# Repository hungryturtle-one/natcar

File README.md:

Natcar is a student design competition created in 1994 by Prof. Richard Spencer and engineers from National Semiconductor. UC Berkeley has been a long-time partner in the event. There is a final competition in May, generally held at UC Davis, in which many schools compete. Teams design, build and race autonomous vehicles on a track marked by 1″-wide white tape.

Originally, there was a wire carrying a 75 kHz sinusoidal signal (100 mA rms) under the tape and many teams sensed the magnetic field around the wire. Since 2016, we no longer provide the wire under the tape and the sensing must be done optically. The contest is intended for undergraduate students, but teams with graduate students, high-school students or student who have competed in a previous Natcar may attend the competition, although they will compete in a separate division.

from https://ece.ucdavis.edu/natcar

Was 6th place in the 2018 competition
https://www.youtube.com/watch?v=erOzUBIFhNc&feature=youtu.be

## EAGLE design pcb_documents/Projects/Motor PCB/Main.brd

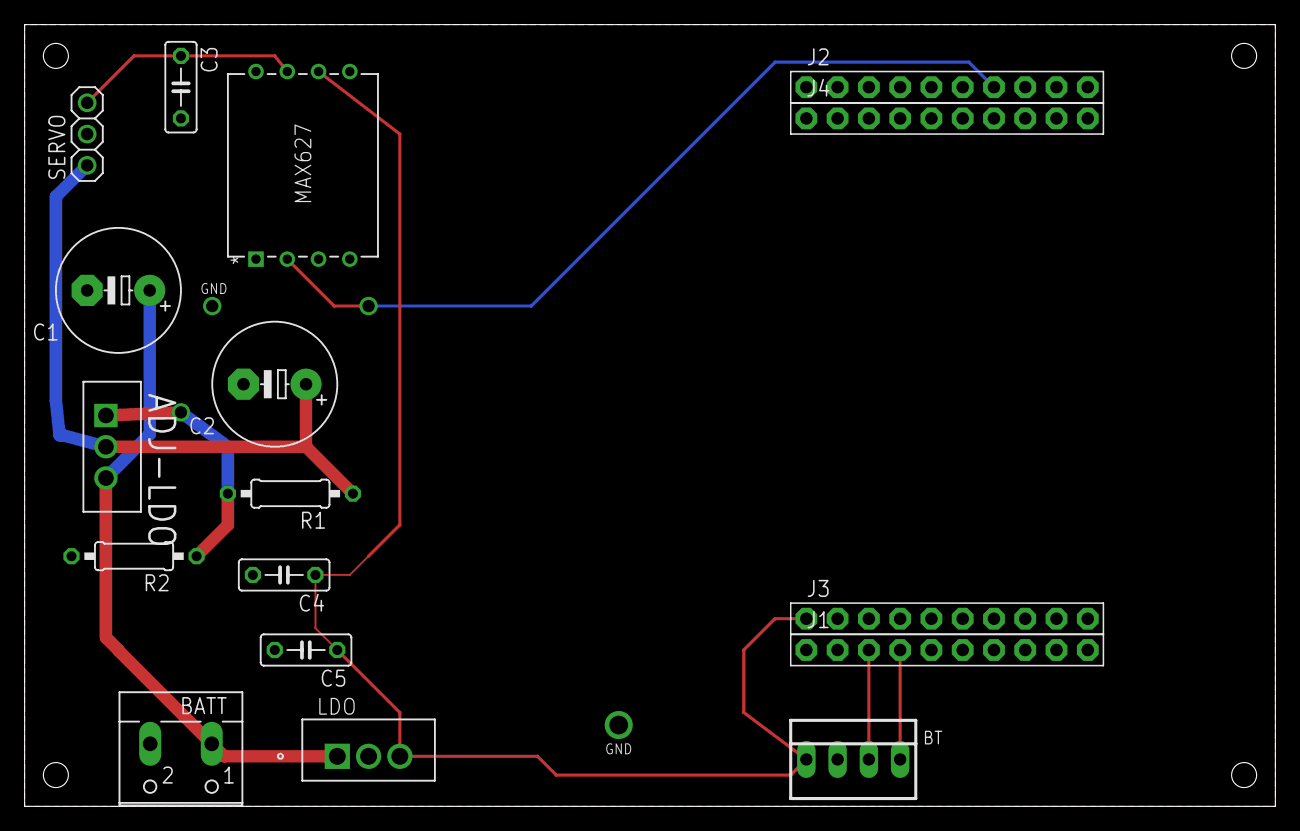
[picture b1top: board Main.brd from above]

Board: 2 copper layers, 101.6 x 63.5 mm, 17 parts (0 on the bottom side), 9 nets.

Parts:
ADJ-LDO: LM1086; TO254P470X1016X2222-3P
BATT: W237-102
BT: 22-23-2041
C1, C2: 10uF; E5-10,5
C3: 1000pF; C050-025X075
C4: 4.7uF; C050-025X075
C5: 0.1uF; C050-025X075
J1, J2, J3, J4: PINHD-1X10; 1X10-BIG
LDO: LM2940T-5.0/NOPB; T03B
MAX627: MAX627CPA; 21-0044B_8
R1: 150; 0207/10
R2: 560; 0207/10
SERVO: 1X03

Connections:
5V: BT.1, C4.1, C5.1, J3.1, LDO.3, MAX627.6
6.0V: ADJ-LDO.2, C2.+, R1.1, SERVO.1
7.2V: ADJ-LDO.3, BATT.1, C1.+, LDO.1
GND: BATT.2, BT.2, C1.-, C2.-, C3.2, C4.2, C5.2, J2.1, J3.2, LDO.2, MAX627.3, MAX627.4, R2.2, SERVO.2
unnamed: BT.3, J1.3
unnamed: BT.4, J1.4
unnamed: ADJ-LDO.1, R1.2, R2.1
PWMIN: J2.7, MAX627.2
PWMOUT: C3.1, MAX627.7, SERVO.3

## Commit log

2020-06-23 added added main from natcar project
2020-06-23 cleanup code
2020-06-23 added pcb documents
2020-06-23 diagram of steering control
